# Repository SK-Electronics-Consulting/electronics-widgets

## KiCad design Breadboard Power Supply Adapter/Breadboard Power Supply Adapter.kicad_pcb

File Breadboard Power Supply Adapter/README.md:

# Breadboard Power Supply Adapter

## Background
I've run into some recurring issues when using bench power supplies with projects under development.  
1. The cables tend to be heavy relative to the project PCB.  
2. I commonly use power supplies that are 4-wire, such as the Keithley 2302.
3. The connections will regularly be pushed into a breadboard, and usually in a sloppy manner.

## Solution
A simple board that breaks out the connections into convenient points.  It will get "anchored" by a breadboard, and provide easy connections.

## Change History

| Version | Status | Notes |
| ------- | ------ | ----- |
| V1      | Built and using.  | First attempt at it.  Lessons learned |
| V2      | Ordered | Removed redundant TPs, added Regulator location |

## Lessons learned

1. 0.8mm Thick board is too flexible for this use.
1. Banana Jack connection points can and should be re-used for Wire connections, and possible Keystone hooks.  
1. Add a 3-pin (In, Gnd, Out) option for a regulator or reference.

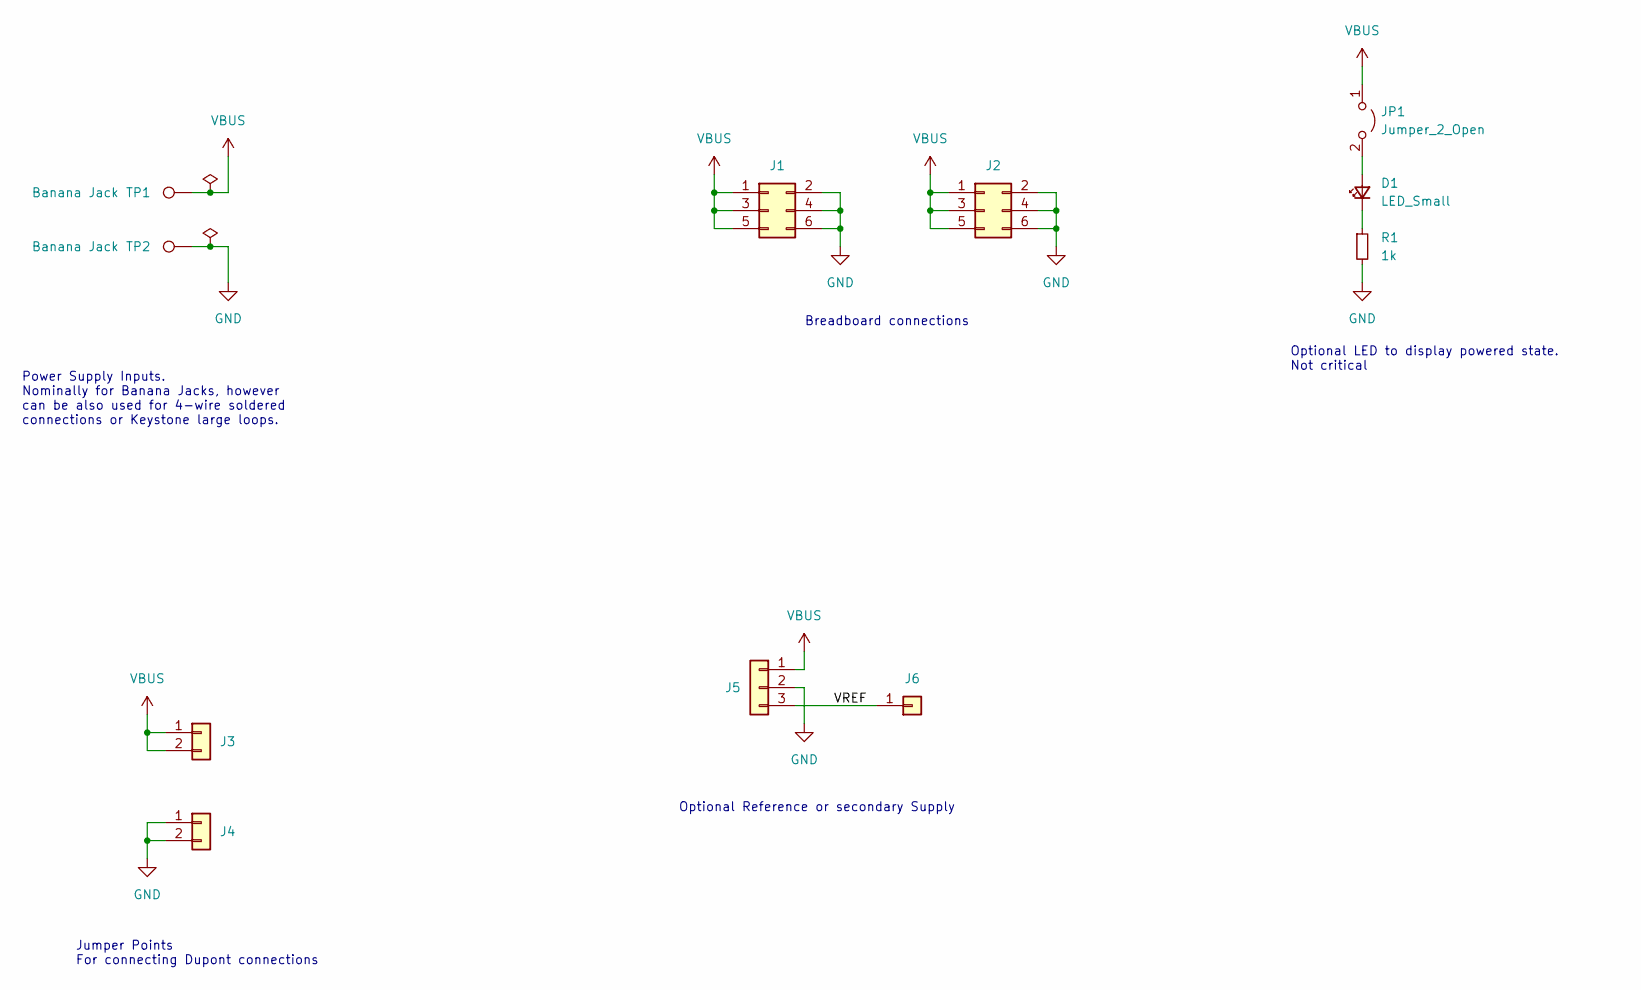
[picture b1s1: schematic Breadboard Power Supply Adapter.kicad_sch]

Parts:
D1: LED_Small; LED_0603_1608Metric_Pad1.05x0.95mm_HandSolder
J1, J2: Conn_02x03_Odd_Even; PinHeader_2x03_P2.54mm_Vertical
J3, J4: Conn_01x02; PinHeader_1x02_P2.54mm_Vertical
J5: Conn_01x03; PinHeader_1x03_P2.54mm_Vertical
J6: Conn_01x01; TestPoint_Keystone_5010-5014_Multipurpose
JP1: Jumper_2_Open; PinHeader_1x02_P2.54mm_Vertical
R1: 1k; R_0603_1608Metric_Pad0.98x0.95mm_HandSolder
TP1, TP2: Banana Jack; CT3151SP

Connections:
/VREF: J5.3, J6.1
GND: J1.2, J1.4, J1.6, J2.2, J2.4, J2.6, J4.1, J4.2, J5.2, R1.2, TP2.1
unnamed: D1.2 (A), JP1.2 (B)
unnamed: D1.1 (K), R1.1
VBUS: J1.1, J1.3, J1.5, J2.1, J2.3, J2.5, J3.1, J3.2, J5.1, JP1.1 (A), TP1.1

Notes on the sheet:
Breadboard connections
Jumper Points For connecting Dupont connections
Optional Reference or secondary Supply
Power Supply Inputs. Nominally for Banana Jacks, however can be also used for 4-wire soldered connections or Keystone large loops.
Optional LED to display powered state. Not critical

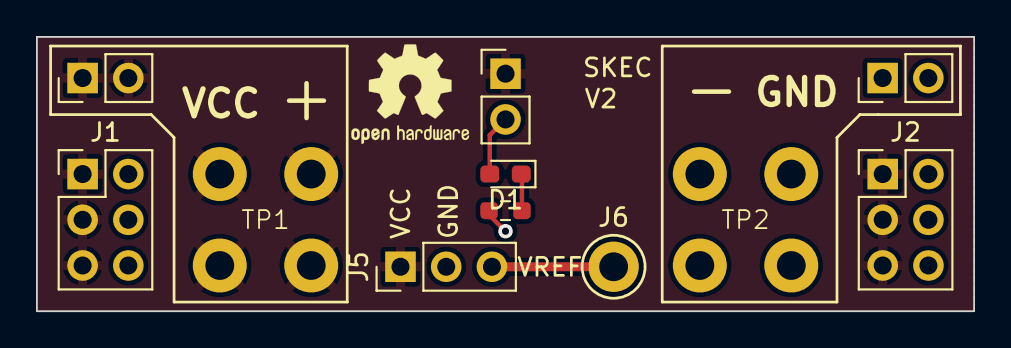
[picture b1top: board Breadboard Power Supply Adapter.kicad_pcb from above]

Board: 2 copper layers, 52.1 x 15.2 mm, 11 parts (0 on the bottom side), 5 nets.

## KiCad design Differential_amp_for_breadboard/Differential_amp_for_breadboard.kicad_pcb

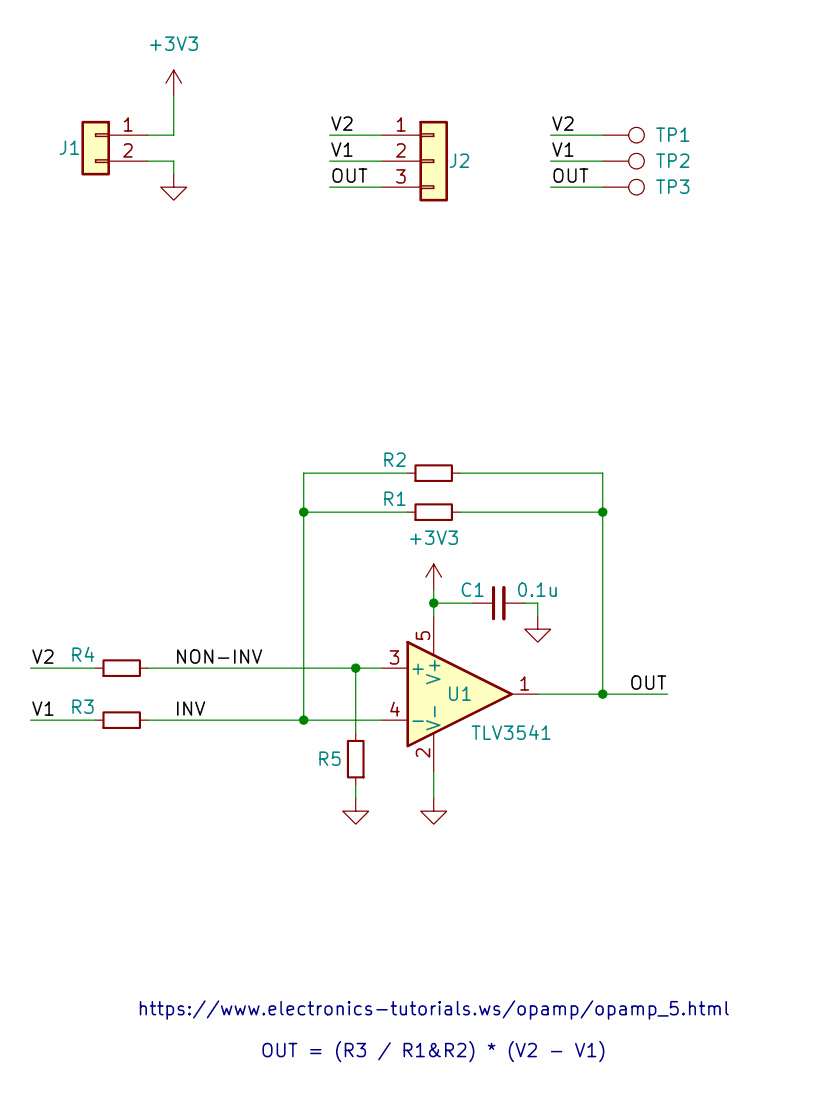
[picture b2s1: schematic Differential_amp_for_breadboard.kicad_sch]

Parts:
C1: 0.1u; C_0402_1005Metric
J1: Conn_01x02; PinHeader_1x02_P2.54mm_Vertical
J2: Conn_01x03; PinHeader_1x03_P2.54mm_Vertical
R1, R2, R3, R4, R5: R_Small; R_0402_1005Metric
TP1, TP2, TP3: TestPoint; TestPoint_Keystone_5000-5004_Miniature
U1: TLV3541; SOT-23-5; MPN TLV3541IDBVR; JLCPCB PN C845577

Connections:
+3V3: C1.1, J1.1, U1.5 (V+)
/INV: R1.1, R2.1, R3.2, U1.4 (-)
/NON-INV: R4.2, R5.2, U1.3 (+)
/OUT: J2.3, R1.2, R2.2, TP3.1, U1.1
/V1: J2.2, R3.1, TP2.1
/V2: J2.1, R4.1, TP1.1
GND: C1.2, J1.2, R5.1, U1.2 (V-)

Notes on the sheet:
https://www.electronics-tutorials.ws/opamp/opamp_5.html OUT = (R3 / R1&R2) * (V2 - V1)

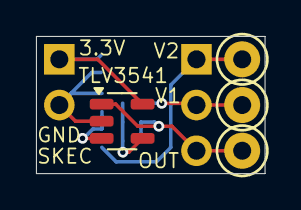
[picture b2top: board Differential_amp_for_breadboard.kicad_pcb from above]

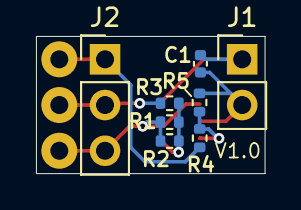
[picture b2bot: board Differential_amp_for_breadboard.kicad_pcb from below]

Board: 4 copper layers, 12.7 x 7.6 mm, 12 parts (8 on the bottom side), 7 nets.

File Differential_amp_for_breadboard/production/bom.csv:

Designator,Footprint,Quantity,Value,LCSC Part #
C1,0402,1,0.1u,
J1,PinHeader_1x02_P2.54mm_Vertical,1,Conn_01x02,
J2,PinHeader_1x03_P2.54mm_Vertical,1,Conn_01x03,
"R1, R2, R3, R4, R5",0402,5,R_Small,
"TP1, TP2, TP3",TestPoint_Keystone_5000-5004_Miniature,3,TestPoint,
U1,SOT-23-5,1,TLV3541,TLV3541IDBVR

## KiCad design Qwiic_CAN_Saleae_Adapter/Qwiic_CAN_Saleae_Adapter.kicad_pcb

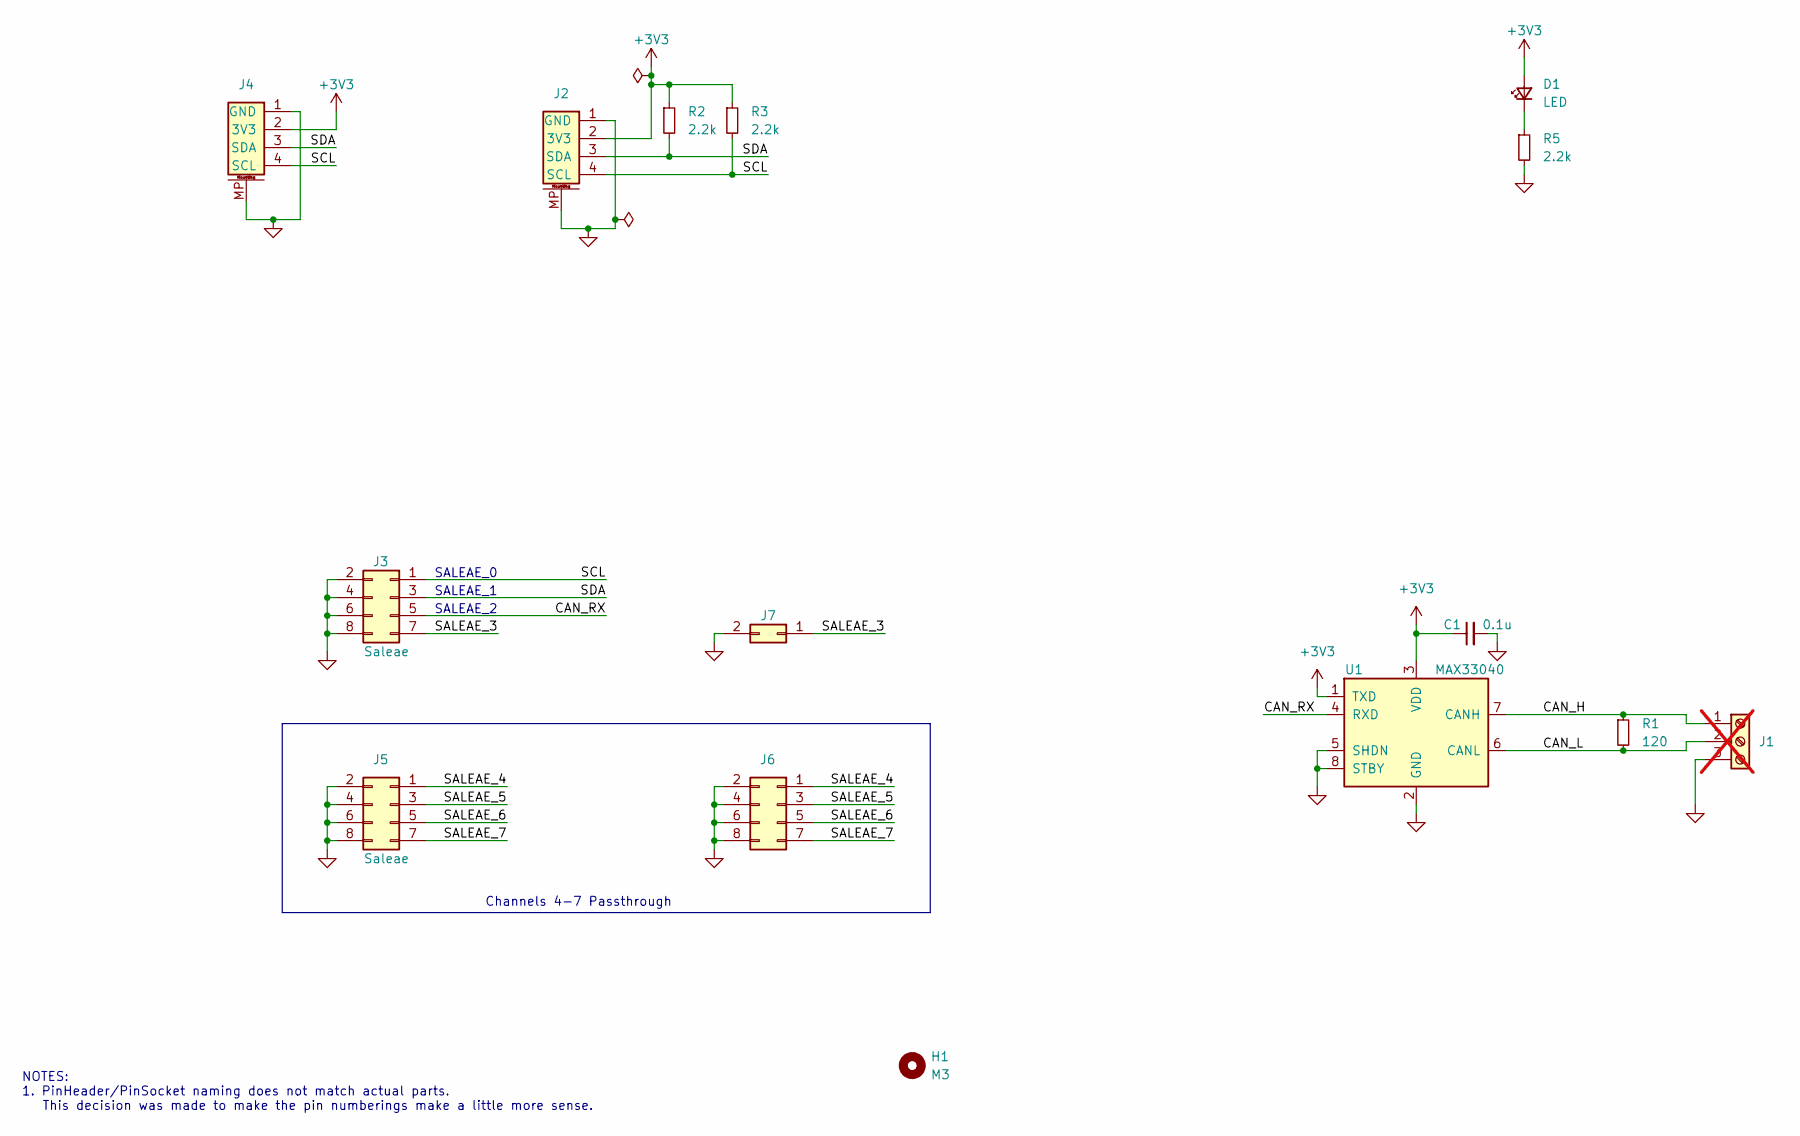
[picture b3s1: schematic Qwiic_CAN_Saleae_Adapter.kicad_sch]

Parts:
C1: 0.1u; C_0402_1005Metric; MPN CC0402KRX7R9BB104; JLCPCB Part No. C131394
D1: LED; LED_0603_1608Metric; MPN LTST-C190KRKT; JLCPCB Part No. C94869
H1: M3; MountingHole_3.2mm_M3_DIN965
J1: Screw_Terminal_01x03; Screw_Terminal_01x03_BoardEdge_Horizontal; MPN C466971; not fitted
J2, J4: Conn_QWIIC_Vertical; JST_SH_BM04B-SRSS-TB_1x04-1MP_P1.00mm_Vertical; MPN BM04B-SRSS-TBT(LF)(SN); Digi-Key 455-BM04B-SRSS-TBTCT-ND
J3, J5: Saleae; PinHeader_2x04_P2.54mm_Horizontal; JLCPCB Part No. C2897424
J6: Saleae; PinSocket_2x04_P2.54mm_Vertical; JLCPCB Part No. C7501275
J7: Conn_02x01; PinSocket_2x01_P2.54mm_Vertical; JLCPCB Part No. C492401
R1: 120; R_0603_1608Metric_Pad0.98x0.95mm_HandSolder; MPN RC0603FR-07120RL; JLCPCB Part No. C114640
R2, R3, R5: 2.2k; R_0402_1005Metric_Pad0.72x0.64mm_HandSolder; JLCPCB Part No. C114762
U1: MAX33040; SOT-23-8; JLCPCB Part No. C5221297

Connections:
+3V3: C1.1, D1.2 (A), J2.2 (3V3), J4.2 (3V3), R2.1, R3.1, U1.1 (TXD), U1.3 (VDD)
/CAN_H: J1.1, R1.1, U1.7 (CANH)
/CAN_L: J1.2, R1.2, U1.6 (CANL)
/CAN_RX: J3.5, U1.4 (RXD)
/SALEAE_3: J3.7, J7.1
/SALEAE_4: J5.1, J6.1
/SALEAE_5: J5.3, J6.3
/SALEAE_6: J5.5, J6.5
/SALEAE_7: J5.7, J6.7
/SCL: J2.4 (SCL), J3.1, J4.4 (SCL), R3.2
/SDA: J2.3 (SDA), J3.3, J4.3 (SDA), R2.2
GND: C1.2, J1.3, J2.1 (GND), J2.MP, J3.2, J3.4, J3.6, J3.8, J4.1 (GND), J4.MP, J5.2, J5.4, J5.6, J5.8, J6.2, J6.4, J6.6, J6.8, J7.2, R5.2, U1.2 (GND), U1.5 (SHDN), U1.8 (STBY)
unnamed: D1.1 (K), R5.1

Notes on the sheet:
NOTES: 1. PinHeader/PinSocket naming does not match actual parts. This decision was made to make the pin numberings make a little more sense.
SALEAE_2
SALEAE_0
Channels 4-7 Passthrough
SALEAE_1

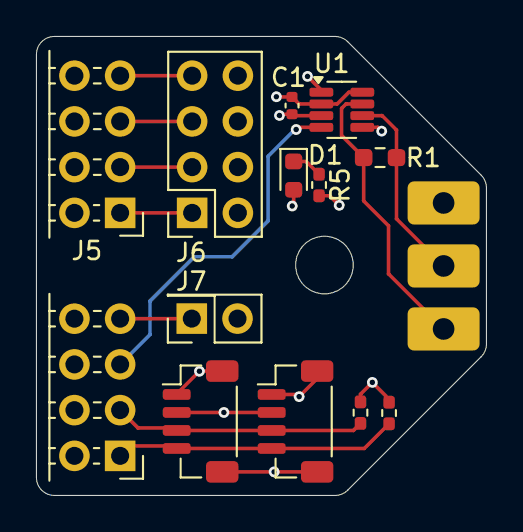
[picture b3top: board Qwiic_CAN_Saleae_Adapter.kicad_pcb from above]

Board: 4 copper layers, 25.0 x 25.5 mm, 15 parts (1 on the bottom side), 13 nets.

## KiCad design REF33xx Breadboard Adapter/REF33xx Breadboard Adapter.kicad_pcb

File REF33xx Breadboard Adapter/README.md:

# REF33xx Breadboard Adapter

## Background

This is a quick breadboard adapter for the REF33xx series of reference.  It includes input and output caps, and nothing more.

## Build status

| Version | Status | Notes |
| ------ | ---- | --- |
| V1 | At Fab | |

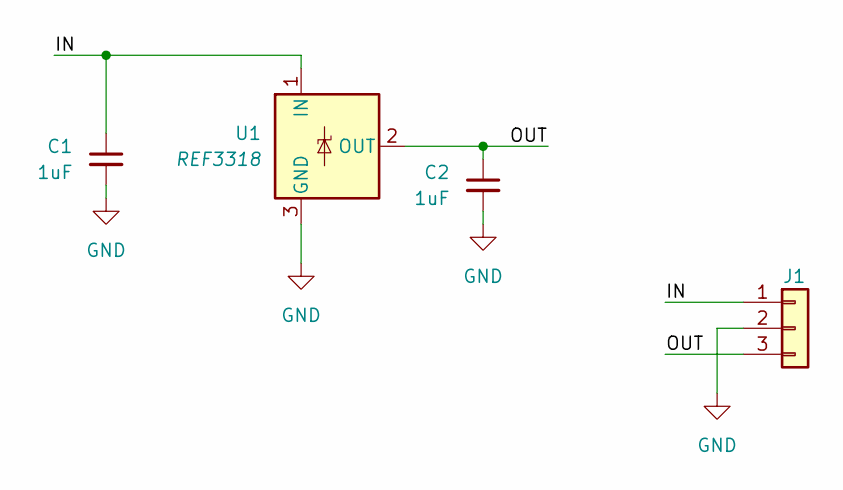
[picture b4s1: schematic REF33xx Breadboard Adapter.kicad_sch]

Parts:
C1, C2: 1uF; C_0603_1608Metric_Pad1.08x0.95mm_HandSolder
J1: Conn_01x03; PinHeader_1x03_P2.54mm_Vertical
U1: REF3318; SOT-23

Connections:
/IN: C1.1, J1.1, U1.1 (IN)
/OUT: C2.1, J1.3, U1.2 (OUT)
GND: C1.2, C2.2, J1.2, U1.3 (GND)

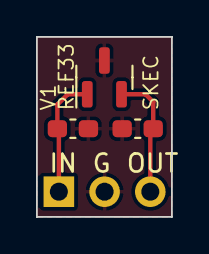
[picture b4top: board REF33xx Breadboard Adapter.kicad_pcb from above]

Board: 2 copper layers, 7.5 x 10.0 mm, 4 parts (1 on the bottom side), 3 nets.

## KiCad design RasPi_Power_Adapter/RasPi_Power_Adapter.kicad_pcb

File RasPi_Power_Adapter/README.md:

# Raspberry Pi Power Adapter

## Background

I needed a better way to provide power to a Raspberry Pi 5 for the HIL Runner setup I'm putting together.  

## Todos

None

## History

V1: First iteration.

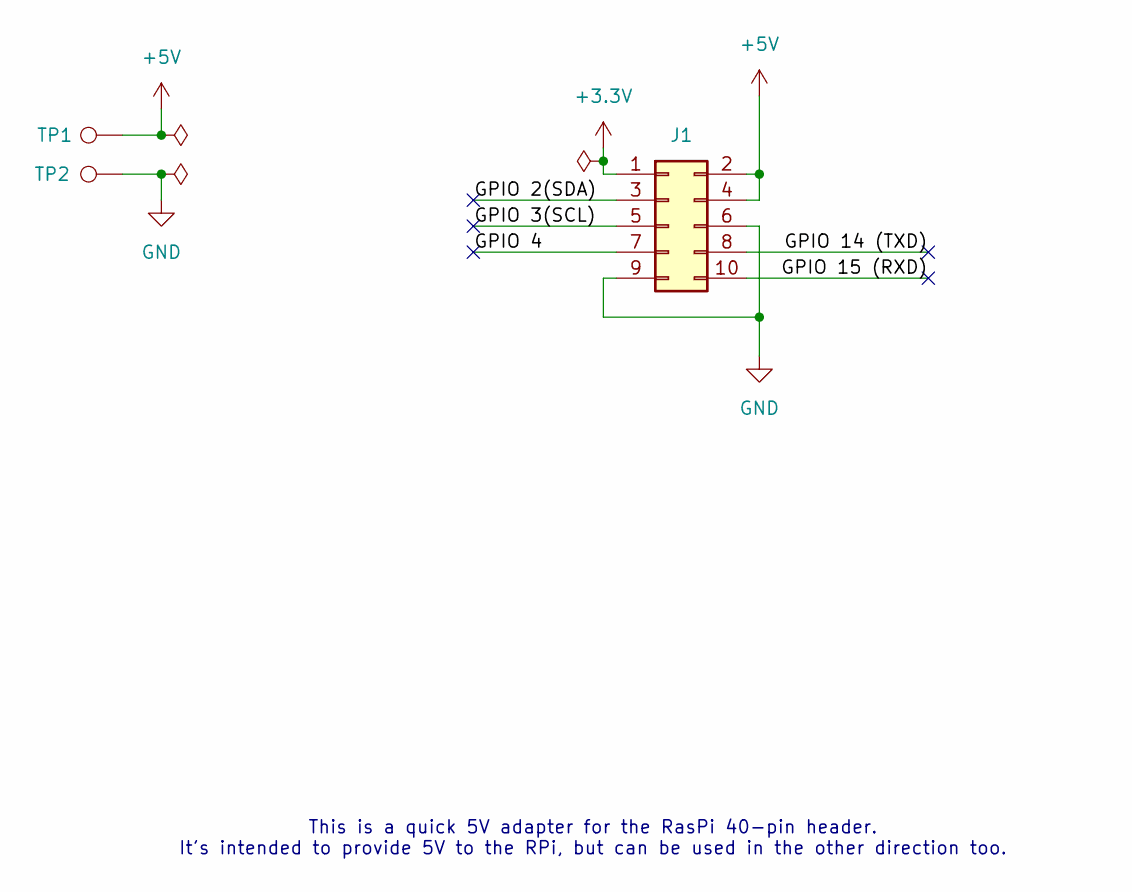
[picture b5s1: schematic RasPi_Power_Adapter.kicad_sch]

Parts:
J1: Conn_02x05_Odd_Even; PinSocket_2x05_P2.54mm_Vertical
TP1, TP2: TestPoint; SolderWire-1sqmm_1x01_D1.4mm_OD2.7mm

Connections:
+3.3V: J1.1
+5V: J1.2, J1.4, TP1.1
/GPIO 2(SDA): J1.3
/GPIO 3(SCL): J1.5
/GPIO 4: J1.7
/GPIO 14 (TXD): J1.8
/GPIO 15 (RXD): J1.10
GND: J1.6, J1.9, TP2.1

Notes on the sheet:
This is a quick 5V adapter for the RasPi 40-pin header. It's intended to provide 5V to the RPi, but can be used in the other direction too.

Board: 2 copper layers, 3 parts (1 on the bottom side), 2 nets, no tracks yet.

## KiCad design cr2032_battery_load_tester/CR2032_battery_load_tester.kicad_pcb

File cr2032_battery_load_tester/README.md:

# CR2032_battery_load_tester

Just a quick and simple board for the sake of making loading and measuring 2032 batteries easier.

Uses the Keystone battery holder, a 100 Ohm resistor, and a button.

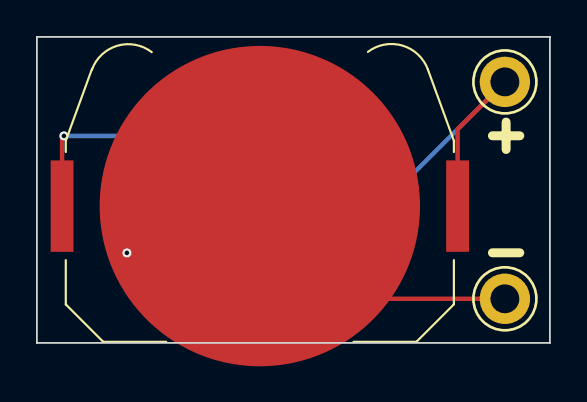
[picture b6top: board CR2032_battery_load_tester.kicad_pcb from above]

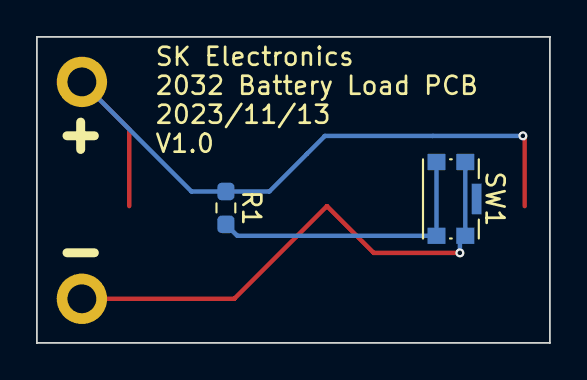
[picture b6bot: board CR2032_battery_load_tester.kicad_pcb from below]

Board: 2 copper layers, 28.5 x 17.0 mm, 5 parts (2 on the bottom side), 3 nets.

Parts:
BT1: Battery_Cell; BatteryHolder_Keystone_3034_1x20mm
R1: 100; R_0603_1608Metric_Pad0.98x0.95mm_HandSolder
SW1: SW_Push; SW_Push_1P1T-SH_NO_CK_KMR2xxG
TP1, TP2: TestPoint; TestPoint_Keystone_5010-5014_Multipurpose

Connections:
+BATT: BT1.1 (+), R1.1, TP1.1
GND: BT1.2 (-), SW1.1, TP2.1
unnamed: R1.2, SW1.2
